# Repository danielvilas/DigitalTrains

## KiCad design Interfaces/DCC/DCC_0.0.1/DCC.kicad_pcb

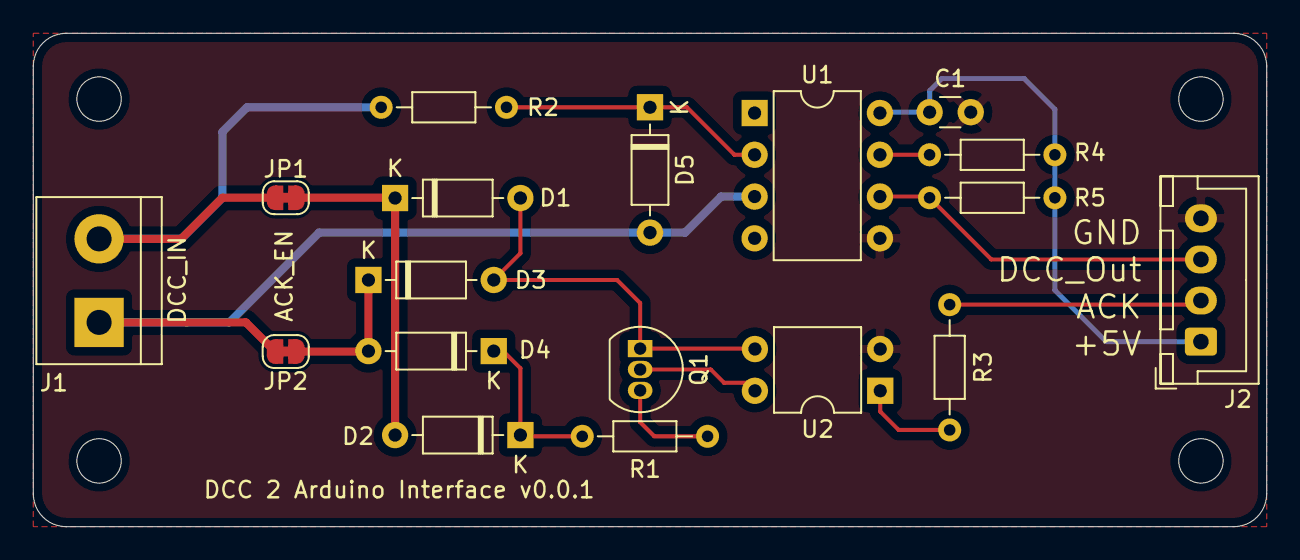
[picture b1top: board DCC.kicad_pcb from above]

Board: 2 copper layers, 75.0 x 30.0 mm, 22 parts (0 on the bottom side), 15 nets.

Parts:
C1: 100uf; C_Disc_D3.0mm_W1.6mm_P2.50mm
D1, D2, D3, D4, D5: 1N4148; D_DO-35_SOD27_P7.62mm_Horizontal
H1, H2, H3, H4: MountingHole; MountingHole_2.7mm_M2.5
J1: Screw_Terminal_01x02; TerminalBlock_bornier-2_P5.08mm
J2: Conn_01x04; JST_XH_B4B-XH-A_1x04_P2.50mm_Vertical
JP1, JP2: Jumper_NC_Small; SolderJumper-2_P1.3mm_Bridged_RoundedPad1.0x1.5mm
Q1: BC560; TO-92_Inline
R1: 100; R_Axial_DIN0204_L3.6mm_D1.6mm_P7.62mm_Horizontal
R2: 3k9; R_Axial_DIN0204_L3.6mm_D1.6mm_P7.62mm_Horizontal
R3: 1K; R_Axial_DIN0204_L3.6mm_D1.6mm_P7.62mm_Horizontal
R4, R5: 10k; R_Axial_DIN0204_L3.6mm_D1.6mm_P7.62mm_Horizontal
U1: 6N137; DIP-8_W7.62mm
U2: PC817; DIP-4_W7.62mm

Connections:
/DCC_IN: J2.3, R5.1, U1.6
/J: J1.2, JP1.2, R2.2
/J_ACK: D1.1, D2.2, JP1.1
/K: D5.2, J1.1, JP2.2, U1.3
/K_ACK: D3.1, D4.2, JP2.1
/ack: J2.2, R3.1
GND: C1.2, J2.4, U1.5, U2.2
unnamed: D1.2, D3.2, Q1.1, U2.3
unnamed: D2.1, D4.1, R1.2
unnamed: D5.1, R2.1, U1.2
unnamed: Q1.2, U2.4
unnamed: Q1.3, R1.1
unnamed: R3.2, U2.1
unnamed: R4.1, U1.7
VCC: C1.1, J2.1, R4.2, R5.2, U1.8

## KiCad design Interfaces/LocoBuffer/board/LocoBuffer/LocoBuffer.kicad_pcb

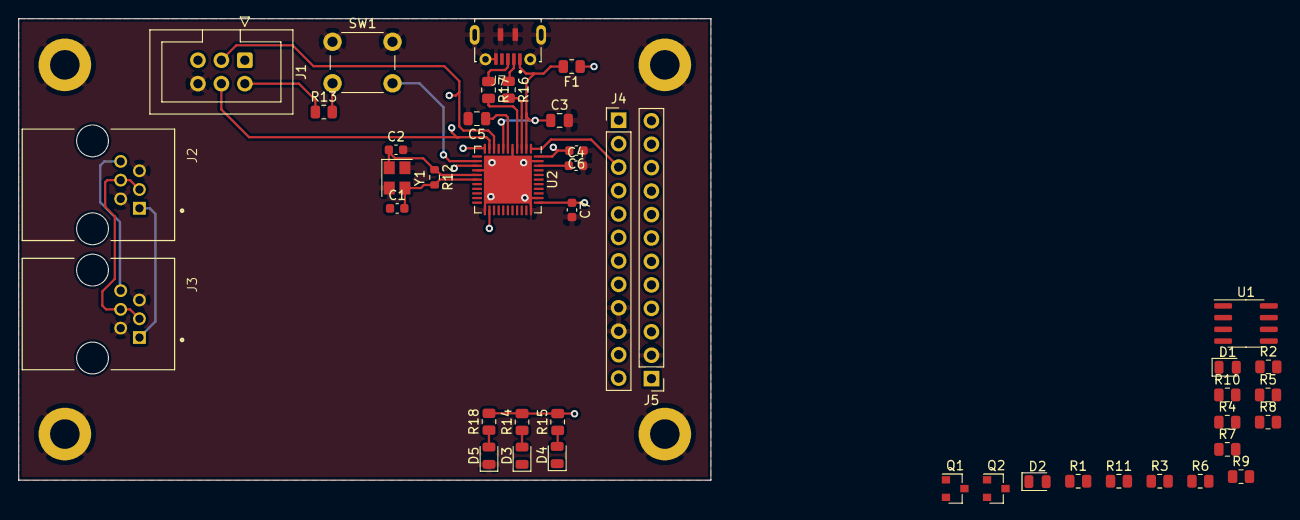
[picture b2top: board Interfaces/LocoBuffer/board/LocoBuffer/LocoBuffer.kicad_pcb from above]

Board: 4 copper layers, 75.0 x 50.0 mm, 47 parts (0 on the bottom side), 46 nets.

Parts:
C1, C2: 22pf; C_0603_1608Metric
C3, C5: 1uf; C_0805_2012Metric
C4, C6, C7: 100nf; C_0603_1608Metric
D1, D2, D3, D4, D5: LED; LED_0805_2012Metric
F1: Polyfuse; R_0805_2012Metric
H1, H2, H3, H4: MountingHole_Pad; MountingHole_3.2mm_M3_ISO7380_Pad
J1: ICSP; IDC-Header_2x03_P2.54mm_Vertical
J2, J3: RJ12; AMPHENOL_RJE0166001
J4, J5: Conn_01x12; PinHeader_1x12_P2.54mm_Vertical
J7: MICROXNJ; SHOUHAN_MICROXNJ
Q1, Q2: 2N3904; SOT-23
R1, R13: 10K; R_0805_2012Metric
R2: 22K; R_0805_2012Metric
R3: 1K; R_0805_2012Metric
R4: 47K; R_0805_2012Metric
R5: 150K; R_0805_2012Metric
R6, R8, R14, R15, R18: 470; R_0805_2012Metric
R7: 220K; R_0805_2012Metric
R9, R11: 4.7K; R_0805_2012Metric
R10: 47; R_0805_2012Metric
R12: 1M; R_0603_1608Metric
R16, R17: 22; R_0805_2012Metric
SW1: SW_Push; SW_PUSH_6mm_H4.3mm
U1: LM311; SOIC-8_3.9x4.9mm_P1.27mm
U2: ATmega32U4-MU; QFN-44-1EP_7x7mm_P0.5mm_EP5.2x5.2mm
Y1: Crystal_GND24; Crystal_SMD_3225-4Pin_3.2x2.5mm

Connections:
/Arduino Leonardo/D+: R17.2, U2.4
/Arduino Leonardo/D-: R16.2, U2.3
/Arduino Leonardo/PB0_D17_SS_RXLED: D3.1, U2.8
/Arduino Leonardo/PB4_D8: J4.2, U2.28
/Arduino Leonardo/PB5_D9_A8: J4.1, U2.29
/Arduino Leonardo/PB6_D10: J5.12, U2.30
/Arduino Leonardo/PC6_D5: J4.5, U2.31
/Arduino Leonardo/PD0_D3_SCL: J4.7, U2.18
/Arduino Leonardo/PD1_D2_SDA: J4.8, U2.19
/Arduino Leonardo/PD2_D0_RX: J4.11, U2.20
/Arduino Leonardo/PD3_D1_TX: J4.12, U2.21
/Arduino Leonardo/PD5_D18_TXLED: D4.1, U2.22
/Arduino Leonardo/PD7_D6_A7: J4.4, U2.27
/Arduino Leonardo/PF4_A3: J5.5, U2.39
/Arduino Leonardo/PF5_A2: J5.6, U2.38
/Arduino Leonardo/PF6_A1: J5.7, U2.37
/Arduino Leonardo/PF7_A0: J5.8, U2.36
/Arduino Leonardo/ap_aref: C4.1, U2.42
/LocoNet/loconet: J2.3, J2.4, J3.3, J3.4, Q2.3, R4.1
/RX: D1.1, J4.6, R3.1, R7.1, U1.7, U2.25
/TX: J4.3, R9.1, R11.1, U2.1
/miso: J1.1, J5.10, U2.11
/mosi: J1.4, J5.11, U2.10
/rst: J1.5, J5.3, R13.2, SW1.2, U2.13
/sck: J1.3, J5.9, U2.9
GND: C2.2, C3.2, C4.2, C5.2, C6.1, C7.2, D5.1, H1.1, H2.1, H3.1, H4.1, J1.6, J2.2, J2.5, J3.2, J3.5, J4.9, J4.10, J5.2, J7.5, J7.S1, J7.S2, J7.S3, J7.S4, J7.S5, J7.S6, Q1.2, R2.2, R5.2, R10.1, SW1.1, U1.1, U1.4, U2.5, U2.15, U2.23, U2.33, U2.35, U2.43, U2.45, Y1.2, Y1.4
unnamed: C1.2, R12.2, U2.17, Y1.3
unnamed: C2.1, R12.1, U2.16, Y1.1
unnamed: C5.1, U2.6
unnamed: D1.2, R6.1
unnamed: D2.1, Q1.3
unnamed: D2.2, R8.1
unnamed: D3.2, R14.1
unnamed: D4.2, R15.1
unnamed: D5.2, R18.1
unnamed: J2.1, J3.1
unnamed: J2.6, J3.6
unnamed: J7.2, R16.1
unnamed: J7.3, R17.1
unnamed: Q1.1, R9.2
unnamed: Q2.1, R11.2
unnamed: Q2.2, R10.2
unnamed: R1.2, R2.1, U1.3
unnamed: R4.2, R5.1, R7.2, U1.2
VBUS: C3.1, F1.2, J7.1, U2.2, U2.7
VCC: C6.2, C7.1, F1.1, J1.2, J5.4, R1.1, R3.2, R6.2, R8.2, R13.1, R14.2, R15.2, R18.2, U1.8, U2.14, U2.24, U2.34, U2.44

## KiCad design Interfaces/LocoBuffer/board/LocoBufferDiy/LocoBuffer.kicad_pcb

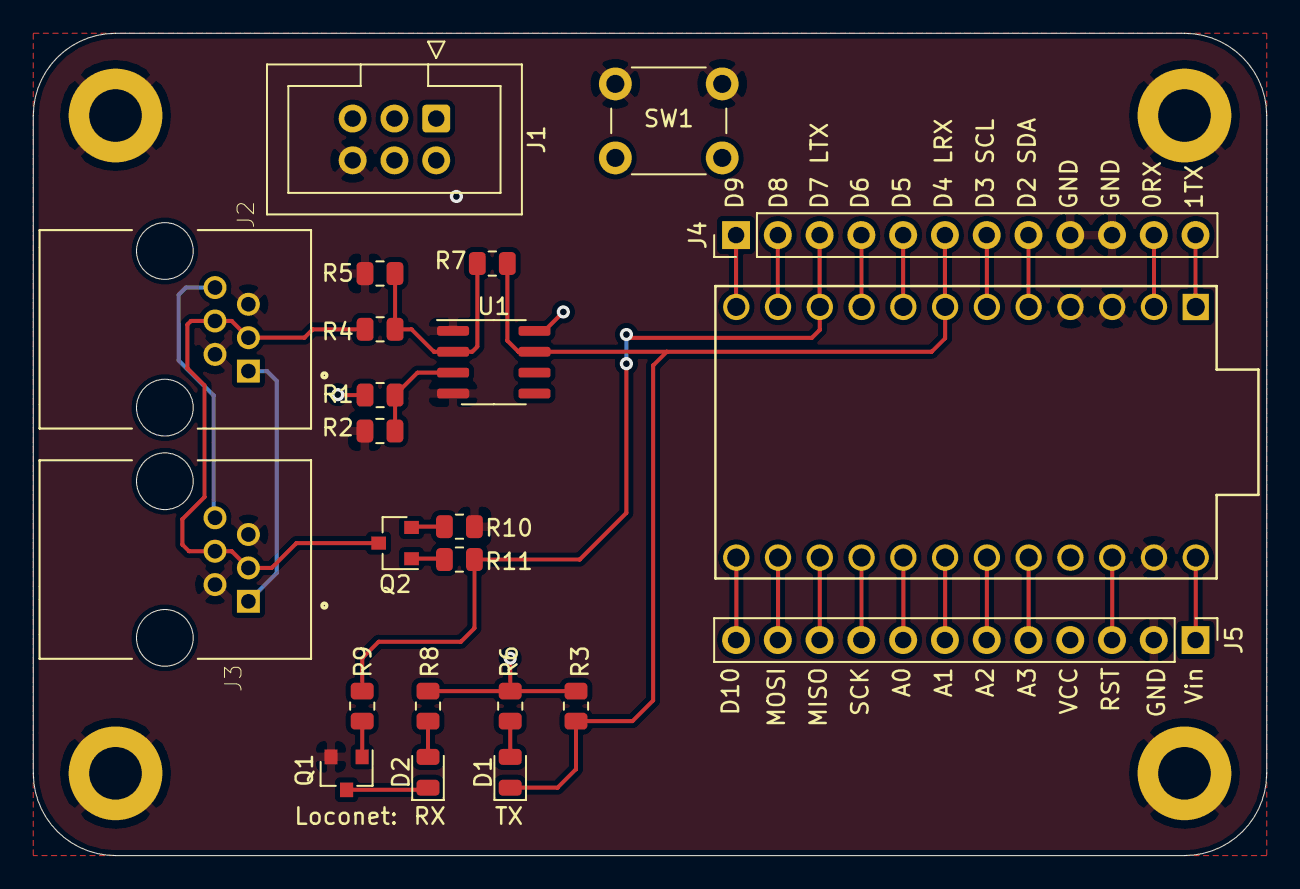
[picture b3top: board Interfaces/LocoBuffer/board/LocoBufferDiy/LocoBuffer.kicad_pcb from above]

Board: 4 copper layers, 75.0 x 50.0 mm, 27 parts (0 on the bottom side), 33 nets.

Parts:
D1, D2: LED; LED_0805_2012Metric
H1, H2, H3, H4: MountingHole_Pad; MountingHole_3.2mm_M3_ISO7380_Pad
J1: ICSP; IDC-Header_2x03_P2.54mm_Vertical
J2, J3: RJ12; AMPHENOL_RJE0166001
J4, J5: Conn_01x12; PinHeader_1x12_P2.54mm_Vertical
Q1, Q2: 2N3904; SOT-23
R1: 10K; R_0805_2012Metric
R2: 22K; R_0805_2012Metric
R3: 1K; R_0805_2012Metric
R4: 47K; R_0805_2012Metric
R5: 150K; R_0805_2012Metric
R6, R8: 470; R_0805_2012Metric
R7: 220K; R_0805_2012Metric
R9, R11: 4.7K; R_0805_2012Metric
R10: 47; R_0805_2012Metric
SW1: SW_Push; SW_PUSH_6mm_H4.3mm
U1: LM311; SOIC-8_3.9x4.9mm_P1.27mm
U3: ProMicro

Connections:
/Arduino Leonardo/PB4_D8: J4.2, U3.11
/Arduino Leonardo/PB5_D9_A8: J4.1, U3.12
/Arduino Leonardo/PB6_D10: J5.12, U3.13
/Arduino Leonardo/PC6_D5: J4.5, U3.8
/Arduino Leonardo/PD0_D3_SCL: J4.7, U3.6
/Arduino Leonardo/PD1_D2_SDA: J4.8, U3.5
/Arduino Leonardo/PD2_D0_RX: J4.11, U3.2
/Arduino Leonardo/PD3_D1_TX: J4.12, U3.1
/Arduino Leonardo/PD7_D6_A7: J4.4, U3.9
/Arduino Leonardo/PF4_A3: J5.5, U3.20
/Arduino Leonardo/PF5_A2: J5.6, U3.19
/Arduino Leonardo/PF6_A1: J5.7, U3.18
/Arduino Leonardo/PF7_A0: J5.8, U3.17
/Arduino Leonardo/raw: J5.1, U3.24
/LocoNet/loconet: J2.3, J2.4, J3.3, J3.4, Q2.3, R4.1
/RX: D1.1, J4.6, R3.1, R7.1, U1.7, U3.7
/TX: J4.3, R9.1, R11.1, U3.10
/miso: J1.1, J5.10, U3.15
/mosi: J1.4, J5.11, U3.14
/rst: J1.5, J5.3, SW1.2, U3.22
/sck: J1.3, J5.9, U3.16
GND: H1.1, H2.1, H3.1, H4.1, J1.6, J2.2, J2.5, J3.2, J3.5, J4.9, J4.10, J5.2, Q1.2, R2.2, R5.2, R10.1, SW1.1, U1.1, U1.4, U3.3, U3.4, U3.23
unnamed: D1.2, R6.1
unnamed: D2.1, Q1.3
unnamed: D2.2, R8.1
unnamed: J2.1, J3.1
unnamed: J2.6, J3.6
unnamed: Q1.1, R9.2
unnamed: Q2.1, R11.2
unnamed: Q2.2, R10.2
unnamed: R1.2, R2.1, U1.3
unnamed: R4.2, R5.1, R7.2, U1.2
VCC: J1.2, J5.4, R1.1, R3.2, R6.2, R8.2, U1.8, U3.21

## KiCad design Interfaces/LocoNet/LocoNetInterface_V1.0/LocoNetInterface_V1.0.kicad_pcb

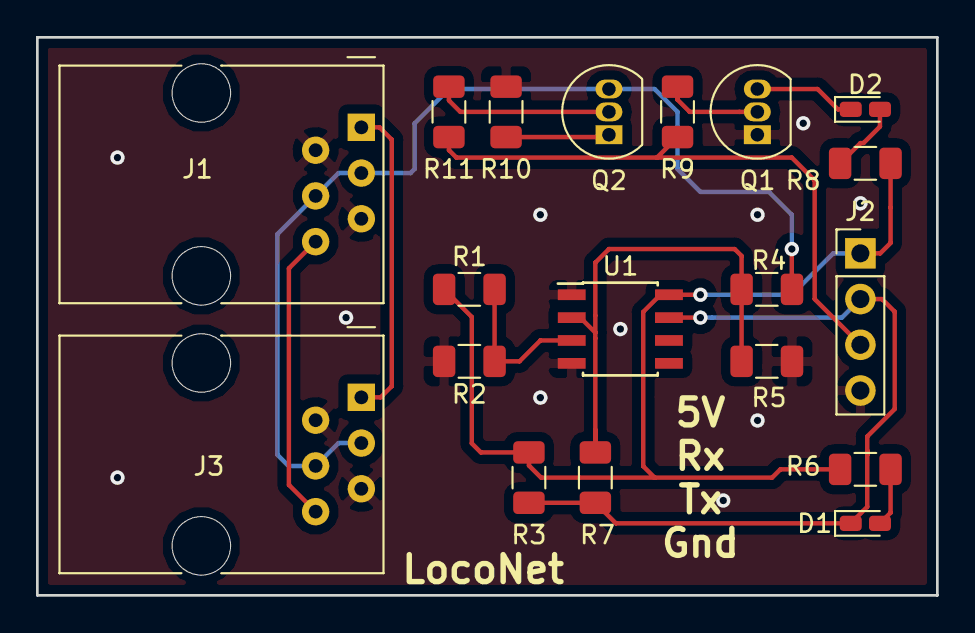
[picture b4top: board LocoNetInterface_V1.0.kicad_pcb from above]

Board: 2 copper layers, 50.0 x 31.0 mm, 19 parts (0 on the bottom side), 15 nets.

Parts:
D1, D2: LED; LED_0603_1608Metric_Castellated
J1, J3: RJ12; RJ12_Amphenol_54601
J2: Conn_01x04; PinHeader_1x04_P2.54mm_Vertical
Q1, Q2: 2N3904; TO-92_Inline
R1: 10K; R_1206_3216Metric
R2: 22K; R_1206_3216Metric
R3: 1K; R_1206_3216Metric
R4: 47K; R_1206_3216Metric
R5: 150K; R_1206_3216Metric
R6, R8: 470; R_1206_3216Metric
R7: 220K; R_1206_3216Metric
R9, R11: 4.7K; R_1206_3216Metric
R10: 47; R_1206_3216Metric
U1: LM311; SOIC-8_3.9x4.9mm_P1.27mm

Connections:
+5V: J2.1, R1.1, R3.2, R6.2, R8.2, U1.8
/RX: D1.1, J2.2, R3.1, R7.1, U1.7
/TX: J2.3, R9.1, R11.1
/loconet: J1.3, J1.4, J3.3, J3.4, Q2.3, R4.1
GND: J1.2, J1.5, J2.4, J3.2, J3.5, Q1.1, R2.2, R5.2, R10.1, U1.1, U1.4
unnamed: D1.2, R6.1
unnamed: D2.1, Q1.3
unnamed: D2.2, R8.1
unnamed: J1.1, J3.1
unnamed: J1.6, J3.6
unnamed: Q1.2, R9.2
unnamed: Q2.1, R10.2
unnamed: Q2.2, R11.2
unnamed: R1.2, R2.1, U1.3
unnamed: R4.2, R5.1, R7.2, U1.2

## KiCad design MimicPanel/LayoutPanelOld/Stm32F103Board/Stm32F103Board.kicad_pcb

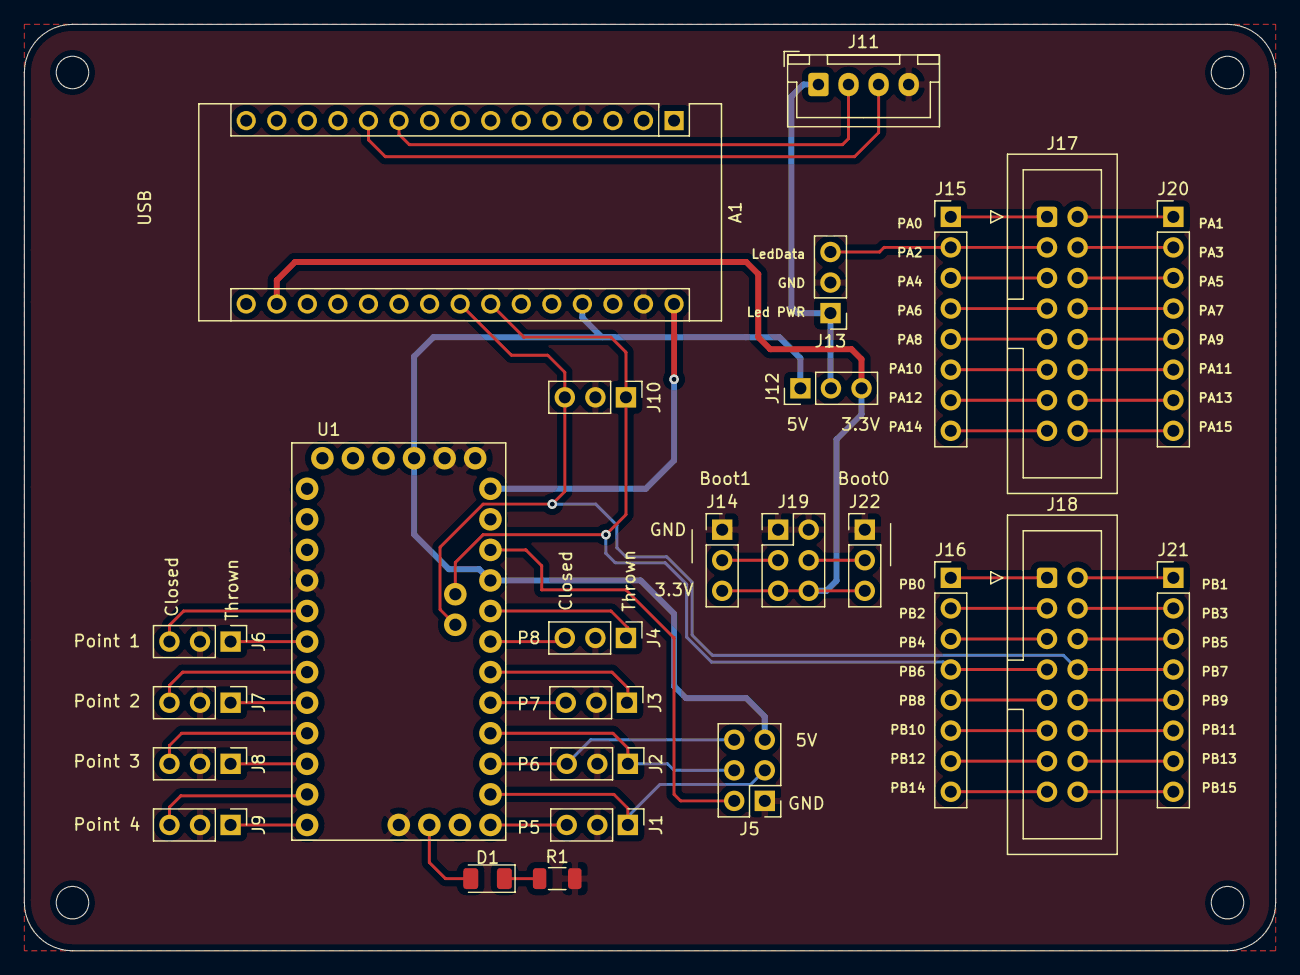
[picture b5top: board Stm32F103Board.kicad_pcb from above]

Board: 2 copper layers, 104.0 x 77.0 mm, 30 parts (0 on the bottom side), 60 nets.

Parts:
A1: Arduino_Nano_v2.x; Arduino_Nano
D1: LED; LED_1206_3216Metric
H1, H2, H3, H4: MountingHole; MountingHole_2.7mm_M2.5
J1, J2, J3, J4, J6, J7, J8, J9, J14, J22: Conn_01x03; PinHeader_1x03_P2.54mm_Vertical
J5, J19: Conn_02x03_Odd_Even; PinHeader_2x03_P2.54mm_Vertical
J10, J12, J13: Conn_01x06; PinHeader_1x03_P2.54mm_Vertical
J11: Conn_01x04; JST_XH_B4B-XH-A_1x04_P2.50mm_Vertical
J15, J16, J20, J21: Conn_01x08; PinHeader_1x08_P2.54mm_Vertical
J17, J18: Conn_02x08_Odd_Even; IDC-Header_2x08_P2.54mm_Vertical
R1: 1K; R_1206_3216Metric
U1: ARDUINO_PRO_MINI; MODULE_ARDUINO_PRO_MINI

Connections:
+3V3: A1.17, J12.3, J14.3, J19.5, J19.6, J22.3
+5V: A1.27, J5.5, J12.1, U1.F_VCC, U1.JP6_4
/Boot0: J19.4, J22.2
/Boot1: J14.2, J19.3
/CSignal: D1.2, U1.JP3_1
/DC_1: J6.3, U1.JP7_8
/DC_2: J7.3, U1.JP7_6
/DC_3: J8.3, U1.JP7_4
/DC_4: J9.3, U1.JP7_2
/DC_5: J1.3, U1.JP6_12
/DC_6: J2.3, J5.6, U1.JP6_10
/DC_7: J3.3, U1.JP6_8
/DC_8: J4.3, U1.JP6_6
/DT_1: J6.1, U1.JP7_7
/DT_2: J7.1, U1.JP7_5
/DT_3: J8.1, U1.JP7_3
/DT_4: J9.1, U1.JP7_1
/DT_5: J1.1, J5.3, U1.JP6_11
/DT_6: J2.1, J5.4, U1.JP6_9
/DT_7: J3.1, U1.JP6_7
/DT_8: J4.1, U1.JP6_5
/LedData: J13.3, J15.2, J17.3
/LedPWR: J11.1, J12.2, J13.1
/Loco_Rx: A1.11, J11.3
/Loco_TX: A1.10, J11.2
/PA0: J15.1, J17.1
/PA1: J17.2, J20.1
/PA3: J17.4, J20.2
/PA4: J15.3, J17.5
/PA5: J17.6, J20.3
/PA6: J15.4, J17.7
/PA7: J17.8, J20.4
/PA8: J15.5, J17.9
/PA9: J17.10, J20.5
/PA10: J15.6, J17.11
/PA11: J17.12, J20.6
/PA12: J15.7, J17.13
/PA13: J17.14, J20.7
/PA14: J15.8, J17.15
/PA15: J17.16, J20.8
/PB0: J16.1, J18.1
/PB1: J18.2, J21.1
/PB2: J16.2, J18.3
/PB3: J18.4, J21.2
/PB4: J16.3, J18.5
/PB5: J18.6, J21.3
/PB6: A1.24, J10.1, J16.4, J18.7, U1.JP2_2
/PB7: A1.23, J10.3, J18.8, J21.4, U1.JP2_1
/PB8: J16.5, J18.9
/PB9: J18.10, J21.5
/PB10: J16.6, J18.11
/PB11: J18.12, J21.6
/PB12: J16.7, J18.13
/PB13: J18.14, J21.7
/PB14: J16.8, J18.15
/PB15: J18.16, J21.8
/Rst_Mini: J5.2, U1.JP6_3
GND: A1.4, A1.29, J1.2, J2.2, J3.2, J4.2, J5.1, J6.2, J7.2, J8.2, J9.2, J10.2, J11.4, J13.2, J14.1, J19.1, J19.2, J22.1, R1.2, U1.F_GND_1, U1.F_GND_2, U1.JP3_3, U1.JP6_2, U1.JP7_9
unnamed: D1.1, R1.1
VBUS: A1.30, U1.JP6_1

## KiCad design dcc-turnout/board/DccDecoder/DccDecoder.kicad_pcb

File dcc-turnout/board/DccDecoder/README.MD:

# Dcc Decoder
This is a Dcc Decoder Module to move a turnout with a Servo

> __WARN__: this folder is a second iteration, to try to model PCB different. and check with version is more addecuate
>
> After testing some iterations only one will be on the repository.

## Desired Specs Status
* ̣[x]Remove Power Distribution to project:  [Power Distribution](../DccBlocks/DccPowerDistribution/)
* [ ] 2 Outputs for LEDs Aspects, to Vin
* [ ] 1 Rele Ouput (5V or 0)
* [x] UART for advanced configuration
* [x] Configure Pins
  * [ ] CV Program to advanced CF
    * [ ] POM if possible
  * [ ] Config mode to capture dcc Address
  * [x] Advanced config mode (2 packets, CV, value)
* [x] Reset Button
* [x] Programing port
  * [ ] Bootloader for uart if possible
  * [ ] if possible no BootX pins
* [x] I2C for EzyBus

## Power Design
First is to determine the power requirments of the diferent main sections, wihch are:

|       |min|expected|max|notes|
|---    |--:|--:|--:|---|
|Servo  | 5 |150|800|idle, run, stall|
|Leds   |10 |20 |40 | underlight, 1led, Both|
|Rele   |0  |80 |100| off, std, +margins|
|MCU    |20 |80 |120|STM32 minum, arduino expected[(1)](https://www.gadgetmakersblog.com/power-consumption-arduinos-atmega328-microcontroller/), +margin|
|Others |10|50|60| extra margins
|**Sum**|45|**380**|*1020*|

In the reality, the max compsution of the servo (Stall) may only occurr when the user is setting up the device. So with this information we can design our power stage, from VDrive to 5V using "WEBENCH Power Designer" indicating we want **1 AMP output** wiht nominal output of **500mA**

## ChangeLog
### v0.1.0
* Initial Version
### v0.2.0
* [x] Buck Converter
* [x] Power Switch with mosfet
### v0.3.0
* [X] D1 FootPrint
* [x] D7 Check stock and review footprint
* [x] Output Connectors, following amps and voltage
* [x] Check 12v DC Jack size with layout
* [X] J7 (Dcc iface) horizontal
* [X] J7 Silk explanation
* [x] J1,J2 and J3, place a bit low and add Mount Hole
* [x] J1,J2 and J3, explain in silk.
* [x] JP* (all) explain in silk (back)
* [x] Dcc iface add jumper Normally Open to isolate 5v rail from buck
* [x] Copy design to new Project (Dcc Power Distributor)
## v0.4.0
* [x] Remove Power Distritubion
* [x Basic MCU
  * [x] MCU
  * [x] SWD
  * [x] Boot 0
* [x] UART.
* [x] I2C
* [x] LEDS
* [x] RELE
* [x] Servo
  * [ ] full
  * [x] enabled
* [x] Config Pins 
## v0.4.1
* [x] Remove 6p SWD
* [x] Return to th SWD

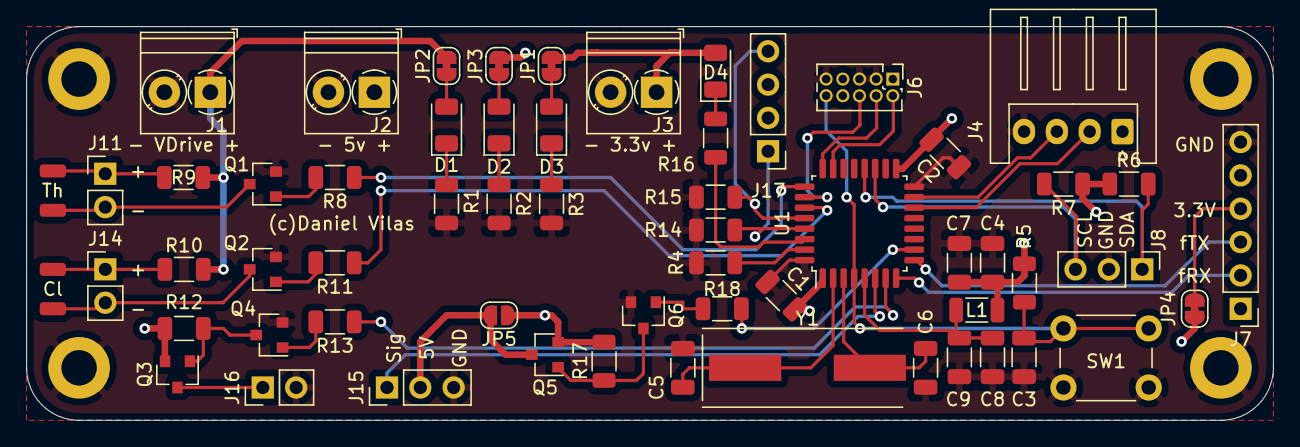
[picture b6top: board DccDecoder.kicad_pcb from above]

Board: 4 copper layers, 95.0 x 30.0 mm, 66 parts (0 on the bottom side), 46 nets.

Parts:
C1, C2, C3: 100nf; C_1206_3216Metric
C4, C8: 1uF; C_1206_3216Metric
C5, C6: 20pf; C_1206_3216Metric
C7, C9: 10nF; C_1206_3216Metric
D1, D2, D3, D4: LED; LED_1206_3216Metric
H1, H2, H3, H4: MountingHole_Pad; MountingHole_2.7mm_M2.5_DIN965_Pad
J1, J2, J3: Conn_01x02; TerminalBlock_Phoenix_PT-1,5-2-3.5-H_1x02_P3.50mm_Horizontal
J4: Conn_01x04; JST_XH_S4B-XH-A_1x04_P2.50mm_Horizontal
J6: Conn_02x05 Odd_Even; PinHeader_2x05_P1.27mm_Vertical
J7: Conn_01x06; PinHeader_1x06_P2.54mm_Vertical
J8, J15: Conn_01x03; PinHeader_1x03_P2.54mm_Vertical
J9, J10, J12, J13: Conn_01x01; SolderWirePad_1x01_SMD_1x2mm
J11, J14, J16: Conn_01x02; PinHeader_1x02_P2.54mm_Vertical
J17: Conn_01x04; PinHeader_1x04_P2.54mm_Vertical
JP1, JP2, JP3, JP4: Jumper_2_Bridged; SolderJumper-2_P1.3mm_Bridged_RoundedPad1.0x1.5mm
JP5: Jumper_2_Open; SolderJumper-2_P1.3mm_Open_RoundedPad1.0x1.5mm
L1: 10uH; L_1206_3216Metric
Q1, Q2, Q4, Q6: NXV55UNR; SOT-23
Q3, Q5: NXV90EPR; SOT-23
R1: 900; R_1206_3216Metric
R2: 200; R_1206_3216Metric
R3, R16: 100; R_1206_3216Metric
R4, R5: 10K; R_1206_3216Metric
R6, R7, R8, R9, R10, R11, R12, R13, R14, R15, R17, R18: 1K; R_1206_3216Metric
SW1: SW_Push; SW_PUSH_6mm
U1: STM32F030K6Tx; LQFP-32_7x7mm_P0.8mm
Y1: 8MHz; HC-49SM8MH

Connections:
+3V3: C1.2, C2.2, C4.1, C7.1, D4.2, J3.1, J6.1, J17.2, J17.3, JP1.2, JP4.2, L1.2, R5.1, R6.1, R7.1, U1.1, U1.17
+5V: J2.1, J4.1, JP3.2, JP5.1, Q3.2, Q5.2, R12.2, R17.2
/CfgAdvanced: J17.4, R15.2, U1.28
/CfgBasic: J17.1, R14.2, U1.29
/CfgStatus: R16.2, U1.30
/ClosedLed: R11.1, U1.27
/F_RX: J7.2, U1.8
/F_TX: J7.3, U1.9
/F_Vcc: J7.4, JP4.1
/Out Puts/_ServoPwr: J15.2, JP5.2, Q5.3
/ReleEn: R13.1, U1.7
/SCL: J8.3, R7.2, U1.19
/SDA: J8.1, R6.2, U1.20
/ServoEn: R18.1, U1.10
/ServoSig: J15.1, U1.6
/ThrownLed: R8.1, U1.25
/_ack: J4.2, U1.14
/_dcc: J4.3, U1.15
/uC 030K6/BOOT0: R4.1, U1.31
/uC 030K6/NRST: C3.1, J6.10, R5.2, SW1.1, U1.4
/uC 030K6/PA13: J6.2, U1.23
/uC 030K6/PA14: J6.4, U1.24
/uC 030K6/PB3: J6.6, U1.26
/uC 030K6/PF0: C5.1, U1.2, Y1.1
/uC 030K6/PF1: C6.1, U1.3, Y1.2
/uC 030K6/_VDDA: C8.1, C9.1, L1.1, U1.5
GND: C1.1, C2.1, C3.2, C4.2, C5.2, C6.2, C7.2, C8.2, C9.2, H1.1, H2.1, H3.1, H4.1, J1.2, J2.2, J3.2, J4.4, J6.3, J6.5, J6.9, J7.6, J8.2, J15.3, J16.2, Q1.2, Q2.2, Q4.2, Q6.2, R1.2, R2.2, R3.2, R4.2, R14.1, R15.1, SW1.2, U1.16, U1.32
unnamed: D1.1, R1.1
unnamed: D1.2, JP2.1
unnamed: D2.1, R2.1
unnamed: D2.2, JP3.1
unnamed: D3.1, R3.1
unnamed: D3.2, JP1.1
unnamed: D4.1, R16.1
unnamed: J10.1, J11.2, Q1.3
unnamed: J9.1, J11.1, R9.1
unnamed: J12.1, J14.1, R10.1
unnamed: J13.1, J14.2, Q2.3
unnamed: J16.1, Q3.3
unnamed: Q1.1, R8.2
unnamed: Q2.1, R11.2
unnamed: Q3.1, Q4.3, R12.1
unnamed: Q4.1, R13.2
unnamed: Q5.1, Q6.3, R17.1
unnamed: Q6.1, R18.2
Vdrive: J1.1, JP2.2, R9.2, R10.2
